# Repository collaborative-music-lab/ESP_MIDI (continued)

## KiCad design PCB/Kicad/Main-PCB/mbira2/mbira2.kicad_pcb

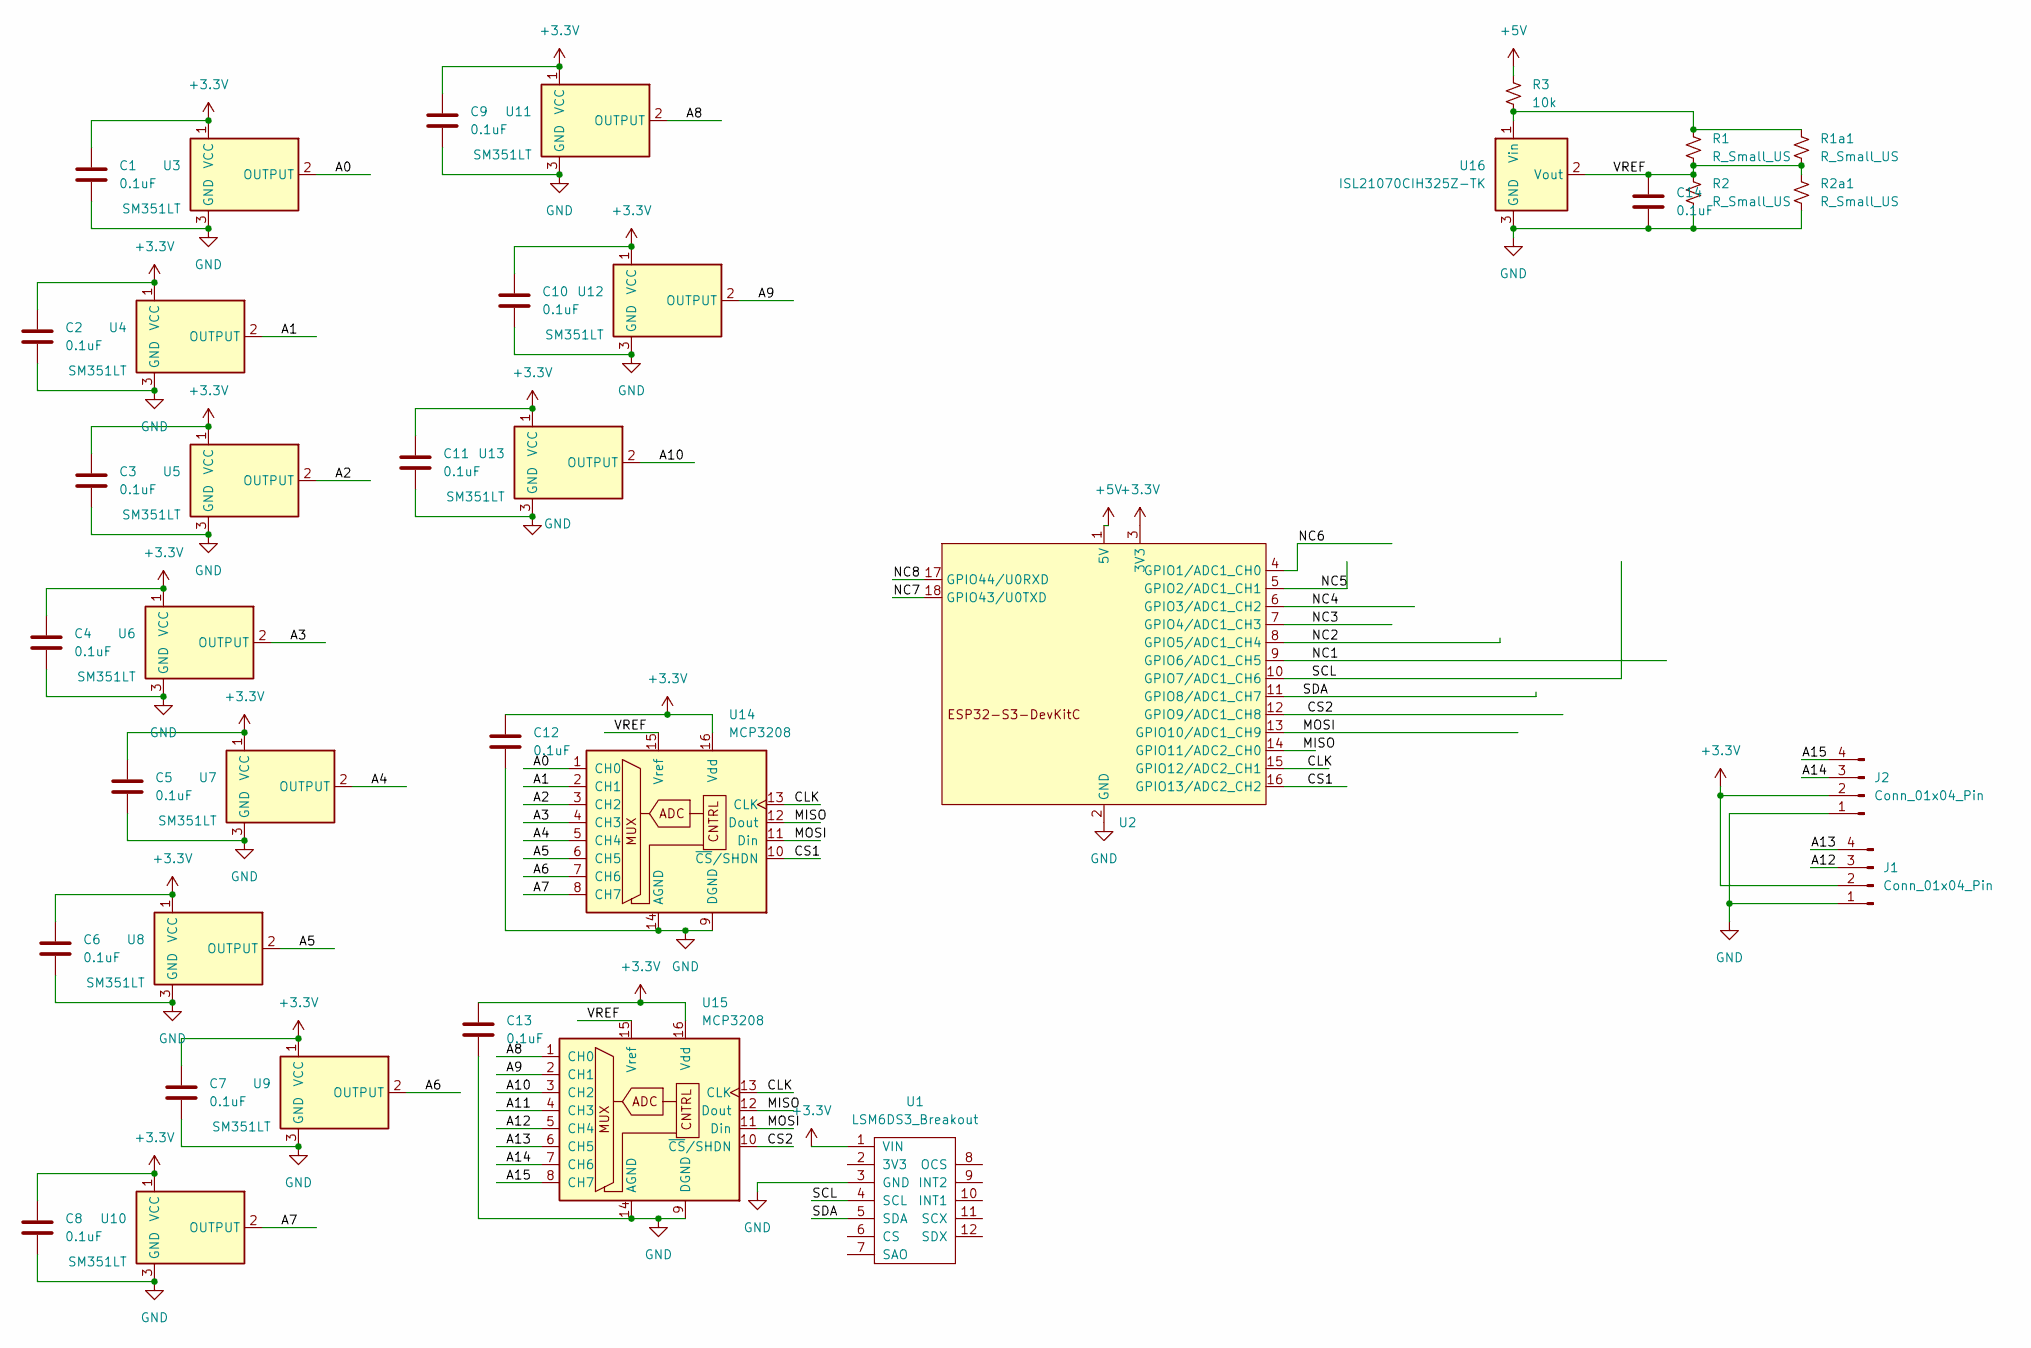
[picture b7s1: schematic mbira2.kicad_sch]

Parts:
C1, C2, C3, C4, C5, C6, C7, C8, C9, C10, C11, C12, C13, C14: 0.1uF; C_0805_2012Metric_Pad1.18x1.45mm_HandSolder
J1, J2: Conn_01x04_Pin; PinHeader_1x04_P1.27mm_Vertical
R1, R2: R_Small_US; R_0805_2012Metric
R1a1, R2a1: R_Small_US; R_Axial_DIN0207_L6.3mm_D2.5mm_P2.54mm_Vertical
R3: 10k; R_0805_2012Metric
U1: LSM6DS3_Breakout; LSM6DS3_Breakout_oneSide
U2: Wifiduino-ESP32S3-SMD
U3, U4, U5, U6, U7, U8, U9, U10, U11, U12, U13: SM351LT; SOT-23
U14, U15: MCP3208; SOIC-16_3.9x9.9mm_P1.27mm
U16: ISL21070CIH325Z-TK; SOT-23

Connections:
+3.3V: C1.1, C2.1, C3.1, C4.1, C5.1, C6.1, C7.1, C8.1, C9.1, C10.1, C11.1, C12.1, C13.1, J1.2, J2.2, U1.1 (VIN), U2.3 (3V3), U3.1 (VCC), U4.1 (VCC), U5.1 (VCC), U6.1 (VCC), U7.1 (VCC), U8.1 (VCC), U9.1 (VCC), U10.1 (VCC), U11.1 (VCC), U12.1 (VCC), U13.1 (VCC), U14.16 (Vdd), U15.16 (Vdd)
+5V: R3.1, U2.1 (5V)
/A0: U3.2 (OUTPUT), U14.1 (CH0)
/A1: U4.2 (OUTPUT), U14.2 (CH1)
/A2: U5.2 (OUTPUT), U14.3 (CH2)
/A3: U6.2 (OUTPUT), U14.4 (CH3)
/A4: U7.2 (OUTPUT), U14.5 (CH4)
/A5: U8.2 (OUTPUT), U14.6 (CH5)
/A6: U9.2 (OUTPUT), U14.7 (CH6)
/A7: U10.2 (OUTPUT), U14.8 (CH7)
/A8: U11.2 (OUTPUT), U15.1 (CH0)
/A9: U12.2 (OUTPUT), U15.2 (CH1)
/A10: U13.2 (OUTPUT), U15.3 (CH2)
/A11: U15.4 (CH3)
/A12: J1.3, U15.5 (CH4)
/A13: J1.4, U15.6 (CH5)
/A14: J2.3, U15.7 (CH6)
/A15: J2.4, U15.8 (CH7)
/CLK: U2.15 (GPIO12/ADC2_CH1), U14.13 (CLK), U15.13 (CLK)
/CS1: U2.16 (GPIO13/ADC2_CH2), U14.10 (~CS/SHDN)
/CS2: U2.12 (GPIO9/ADC1_CH8), U15.10 (~CS/SHDN)
/MISO: U2.14 (GPIO11/ADC2_CH0), U14.12 (Dout), U15.12 (Dout)
/MOSI: U2.13 (GPIO10/ADC1_CH9), U14.11 (Din), U15.11 (Din)
/NC1: U2.9 (GPIO6/ADC1_CH5)
/NC2: U2.8 (GPIO5/ADC1_CH4)
/NC3: U2.7 (GPIO4/ADC1_CH3)
/NC4: U2.6 (GPIO3/ADC1_CH2)
/NC5: U2.5 (GPIO2/ADC1_CH1)
/NC6: U2.4 (GPIO1/ADC1_CH0)
/NC7: U2.18 (GPIO43/U0TXD)
/NC8: U2.17 (GPIO44/U0RXD)
/SCL: U1.4 (SCL), U2.10 (GPIO7/ADC1_CH6)
/SDA: U1.5 (SDA), U2.11 (GPIO8/ADC1_CH7)
/VREF: C14.1, R1.2, R1a1.2, R2.1, R2a1.1, U14.15 (Vref), U15.15 (Vref), U16.2 (Vout)
GND: C1.2, C2.2, C3.2, C4.2, C5.2, C6.2, C7.2, C8.2, C9.2, C10.2, C11.2, C12.2, C13.2, C14.2, J1.1, J2.1, R2.2, R2a1.2, U1.3 (GND), U2.2 (GND), U3.3 (GND), U4.3 (GND), U5.3 (GND), U6.3 (GND), U7.3 (GND), U8.3 (GND), U9.3 (GND), U10.3 (GND), U11.3 (GND), U12.3 (GND), U13.3 (GND), U14.9 (DGND), U14.14 (AGND), U15.9 (DGND), U15.14 (AGND), U16.3 (GND)
unnamed: R1.1, R1a1.1, R3.2, U16.1 (Vin)

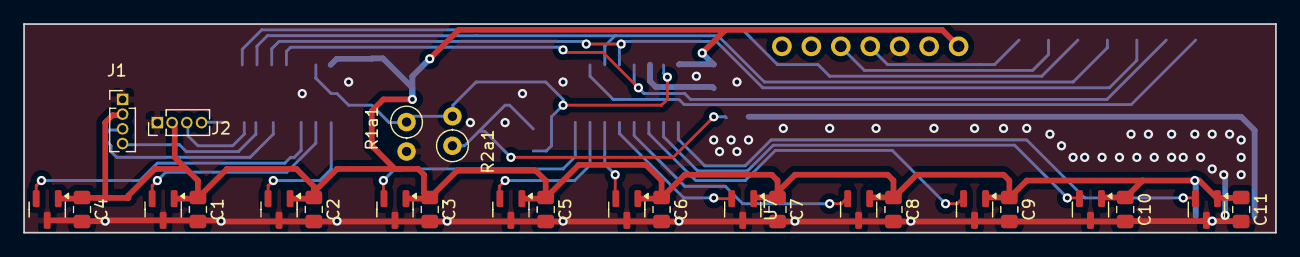
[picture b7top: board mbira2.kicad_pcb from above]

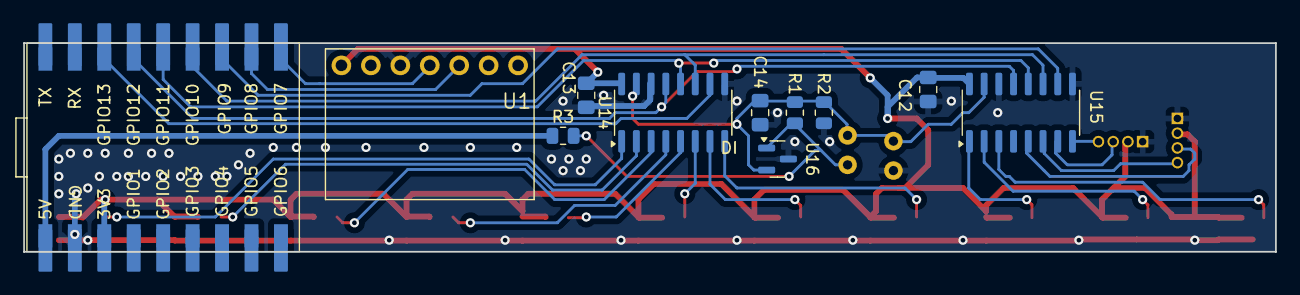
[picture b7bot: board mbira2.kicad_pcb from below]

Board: 2 copper layers, 108.0 x 18.0 mm, 37 parts (11 on the bottom side), 27 nets.

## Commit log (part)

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2024-06-20 initial gerbers
2024-06-27 Create analogRead test sketch
2024-06-27 update simple_midi_imu
2024-06-27 update PCBs
2024-07-09 adding v2 PCB
2024-07-09 Adding simple IMU sketches
2024-07-09 update folder structure
2024-07-09 Added enclosure elements
2024-07-09 Update PCB files
2024-07-11 update firmware and faceplates
2024-07-11 Create readme.md
    To Do:
    - add link for Arduino installer
    - add link for esp32 definition
2024-07-15 Updating enclosures
2024-07-15 adding readmes
2024-07-15 remove redundant firmware
2024-07-15 session 1 notes
2024-07-16 limit sending IMU data
2024-07-16 added web audio examples
2024-07-16 fix scope
2024-12-20 Jan 24 v1
2025-01-10 Jan 10 commit - up to v4
2025-01-13 kicad refresh
2025-01-14 added v5
2025-01-19 added v6 with new USBMIDI
2025-01-20 Switched to new library and added LED midi messages
2025-01-21 update v6
2025-01-21 getting up to date
2025-01-24 Added back led responsiveness on startup
2025-06-22 firmware
2025-06-30 added wand and barre
2025-07-03 update all kicad designs for week 1
2025-07-11 files Jul 10
2025-07-13 semifinal code for summer25
2025-07-14 final wand
2025-07-14 final firmware
2025-07-16 wand v2_1
2025-07-23 added touch v1_1
2025-07-27 July 26 gerbers
2025-07-31 tweaking capsense settings and imu values
2025-08-02 Robin v2 with binary
2025-08-03 added support for BMI160
2025-08-05 adding midi buffering
2025-09-01 add USB device name
2025-09-01 robin and strip PCB updates
2025-09-01 Add strip firmware
2026-02-26 lots of pcb updates!
2026-06-07 created instruments
2026-06-08 robin
2026-06-09 robin aulos
2026-06-10 aulos
2026-06-12 default dac mbira
2026-06-12 esp-now class
2026-06-17 esp-now and robin
2026-06-17 espmidi2cv_v2
2026-06-17 mbira
2026-06-17 robin and midi handler
2026-06-23 new trigger algorithm
2026-06-25 robin updates
